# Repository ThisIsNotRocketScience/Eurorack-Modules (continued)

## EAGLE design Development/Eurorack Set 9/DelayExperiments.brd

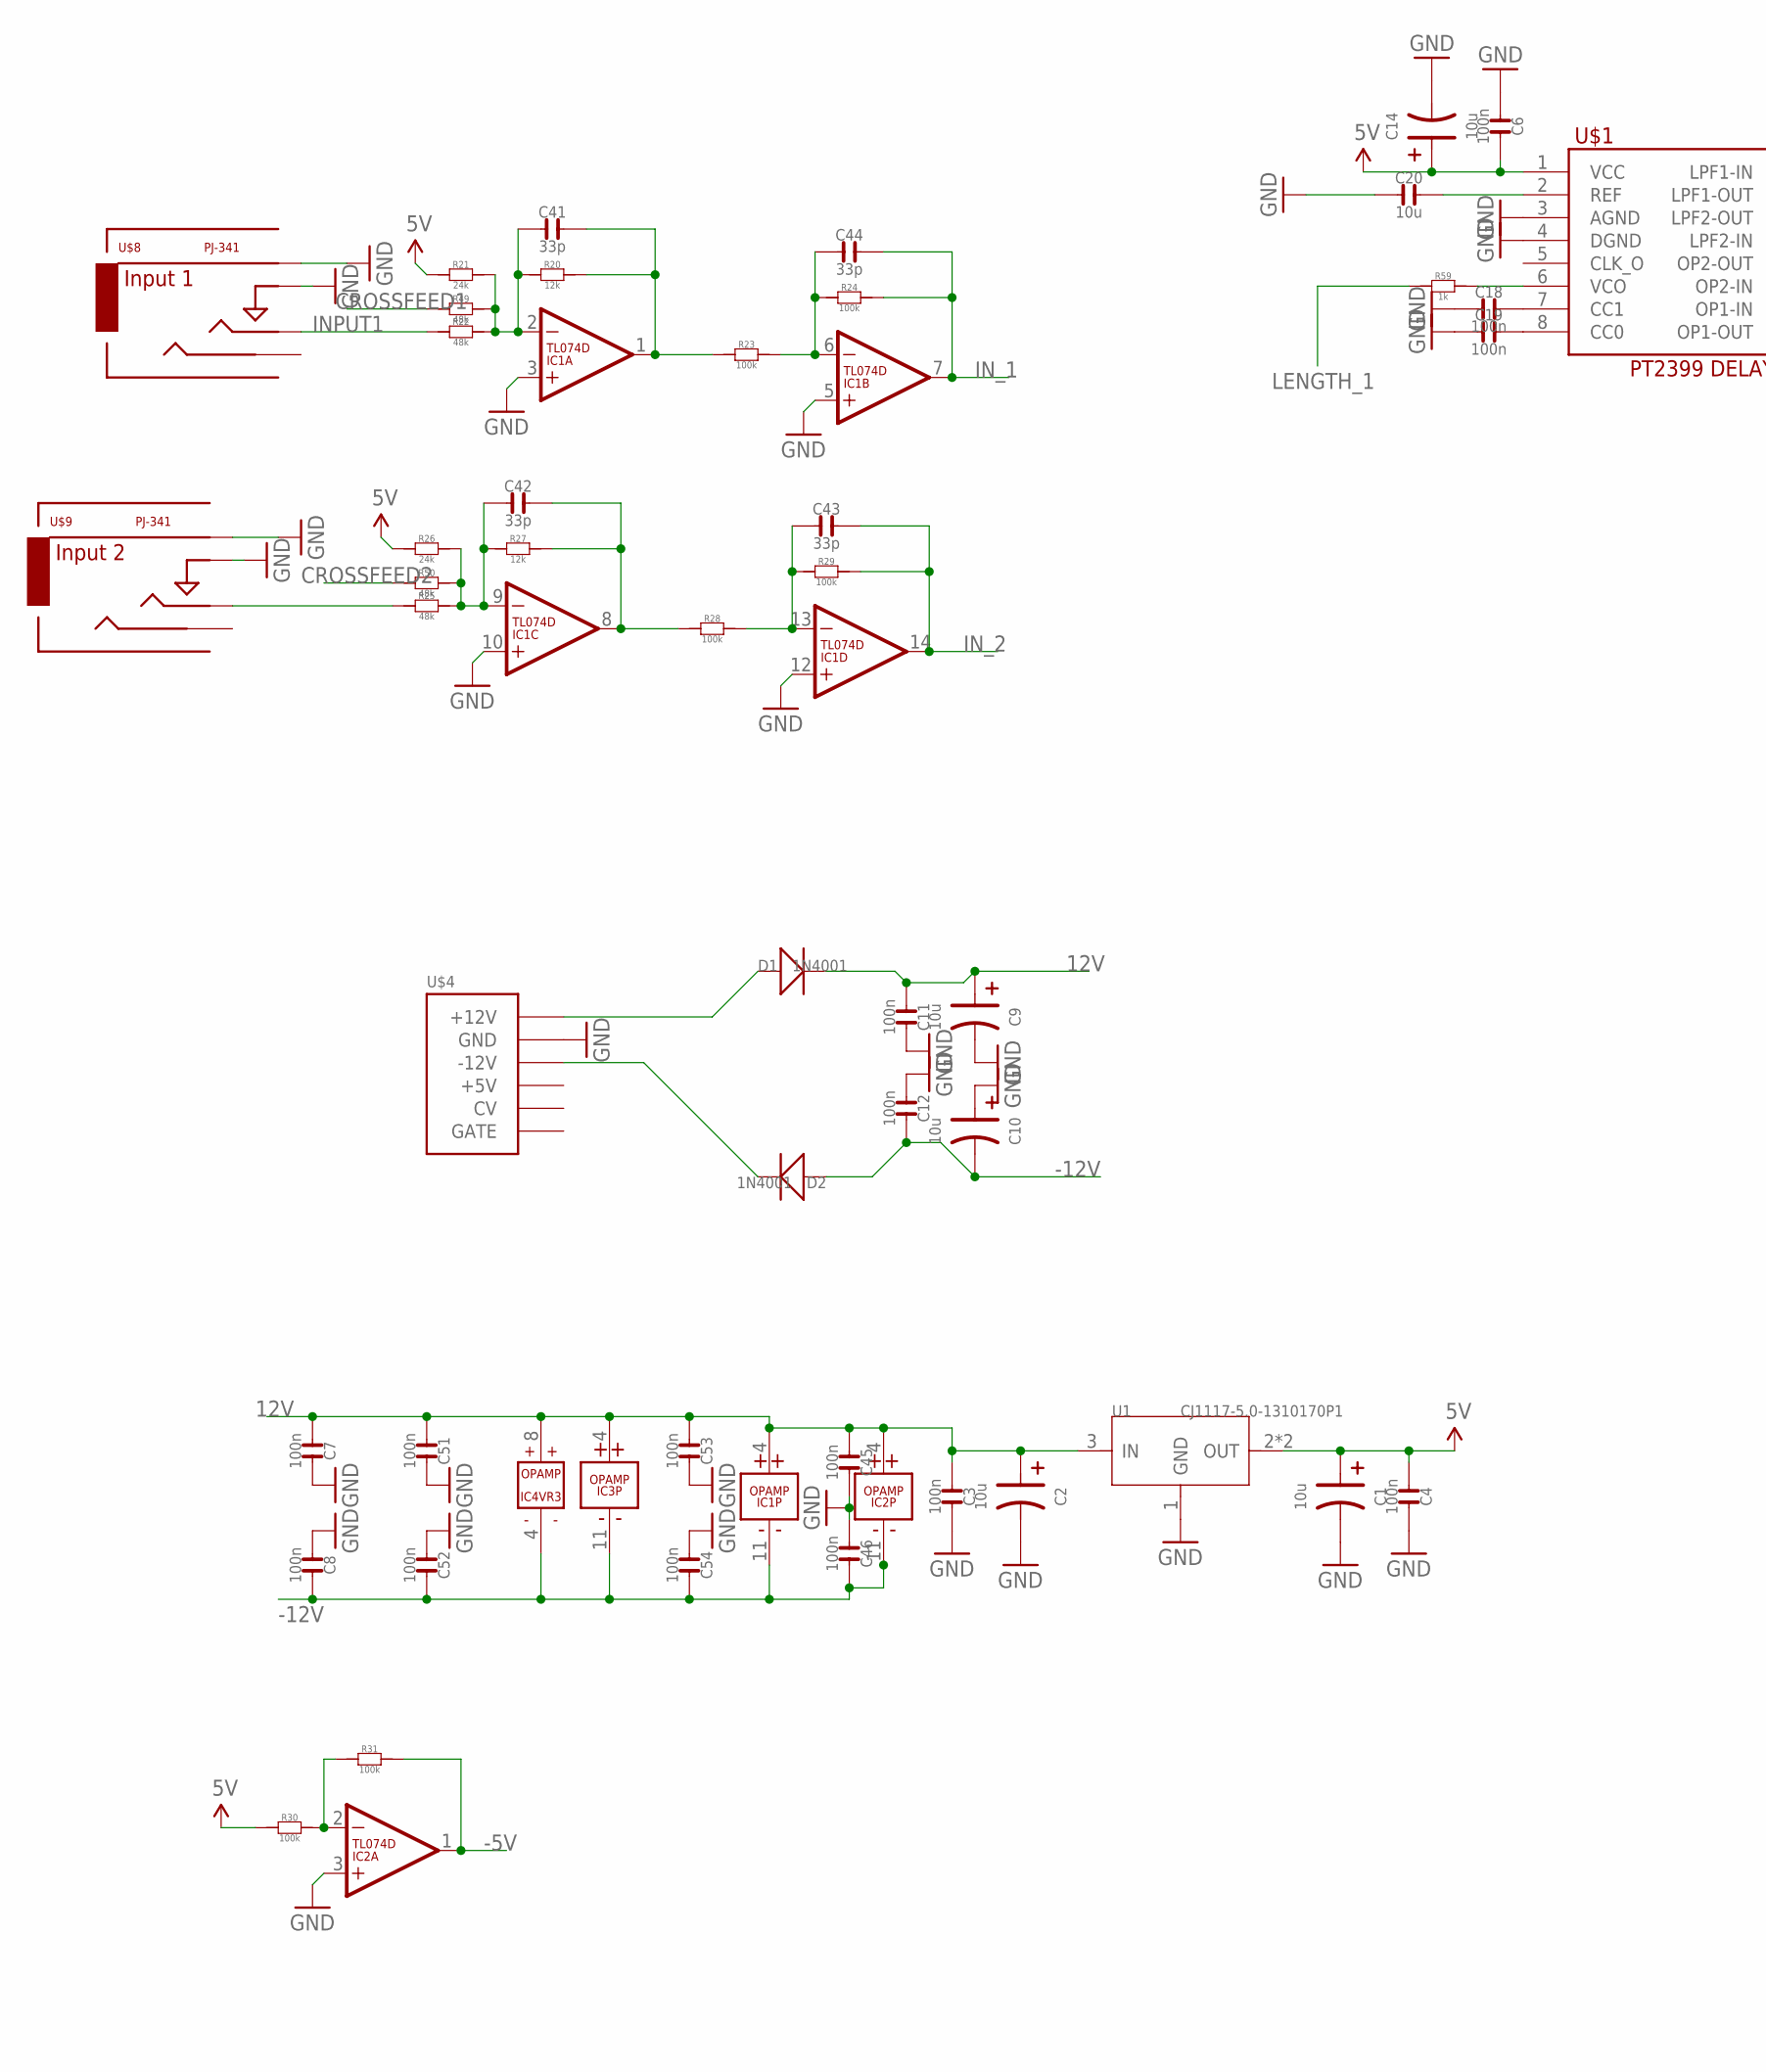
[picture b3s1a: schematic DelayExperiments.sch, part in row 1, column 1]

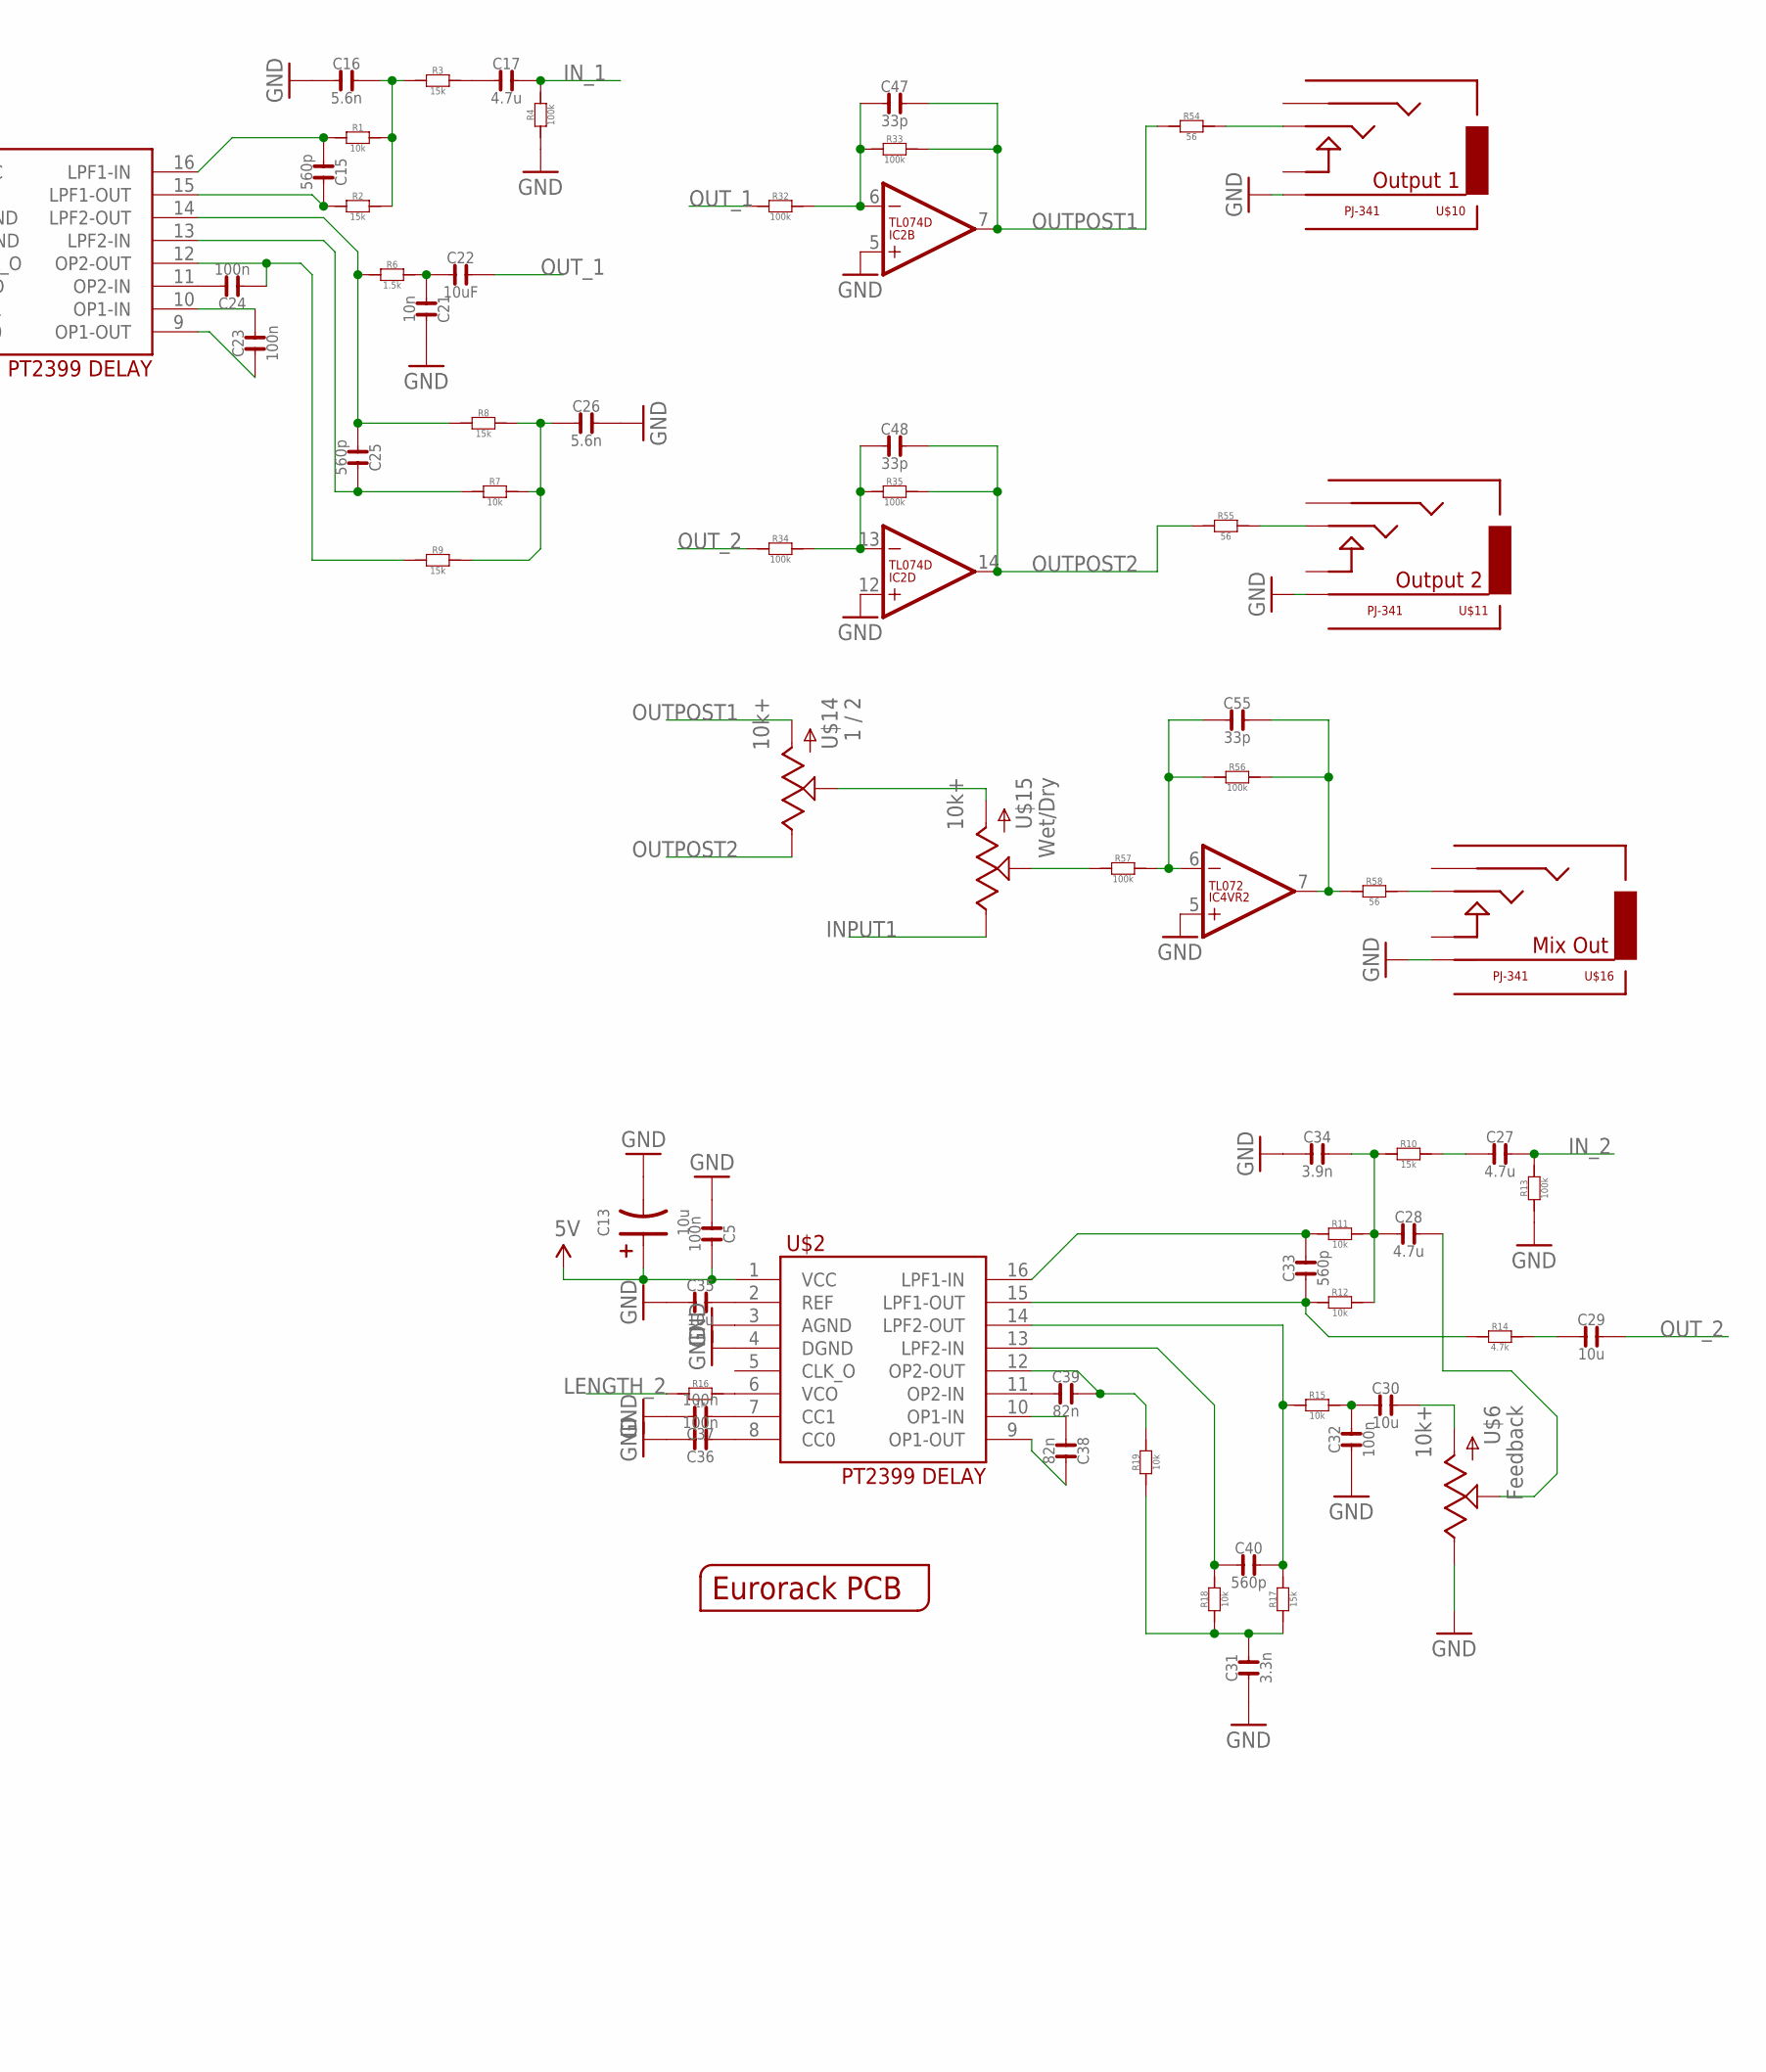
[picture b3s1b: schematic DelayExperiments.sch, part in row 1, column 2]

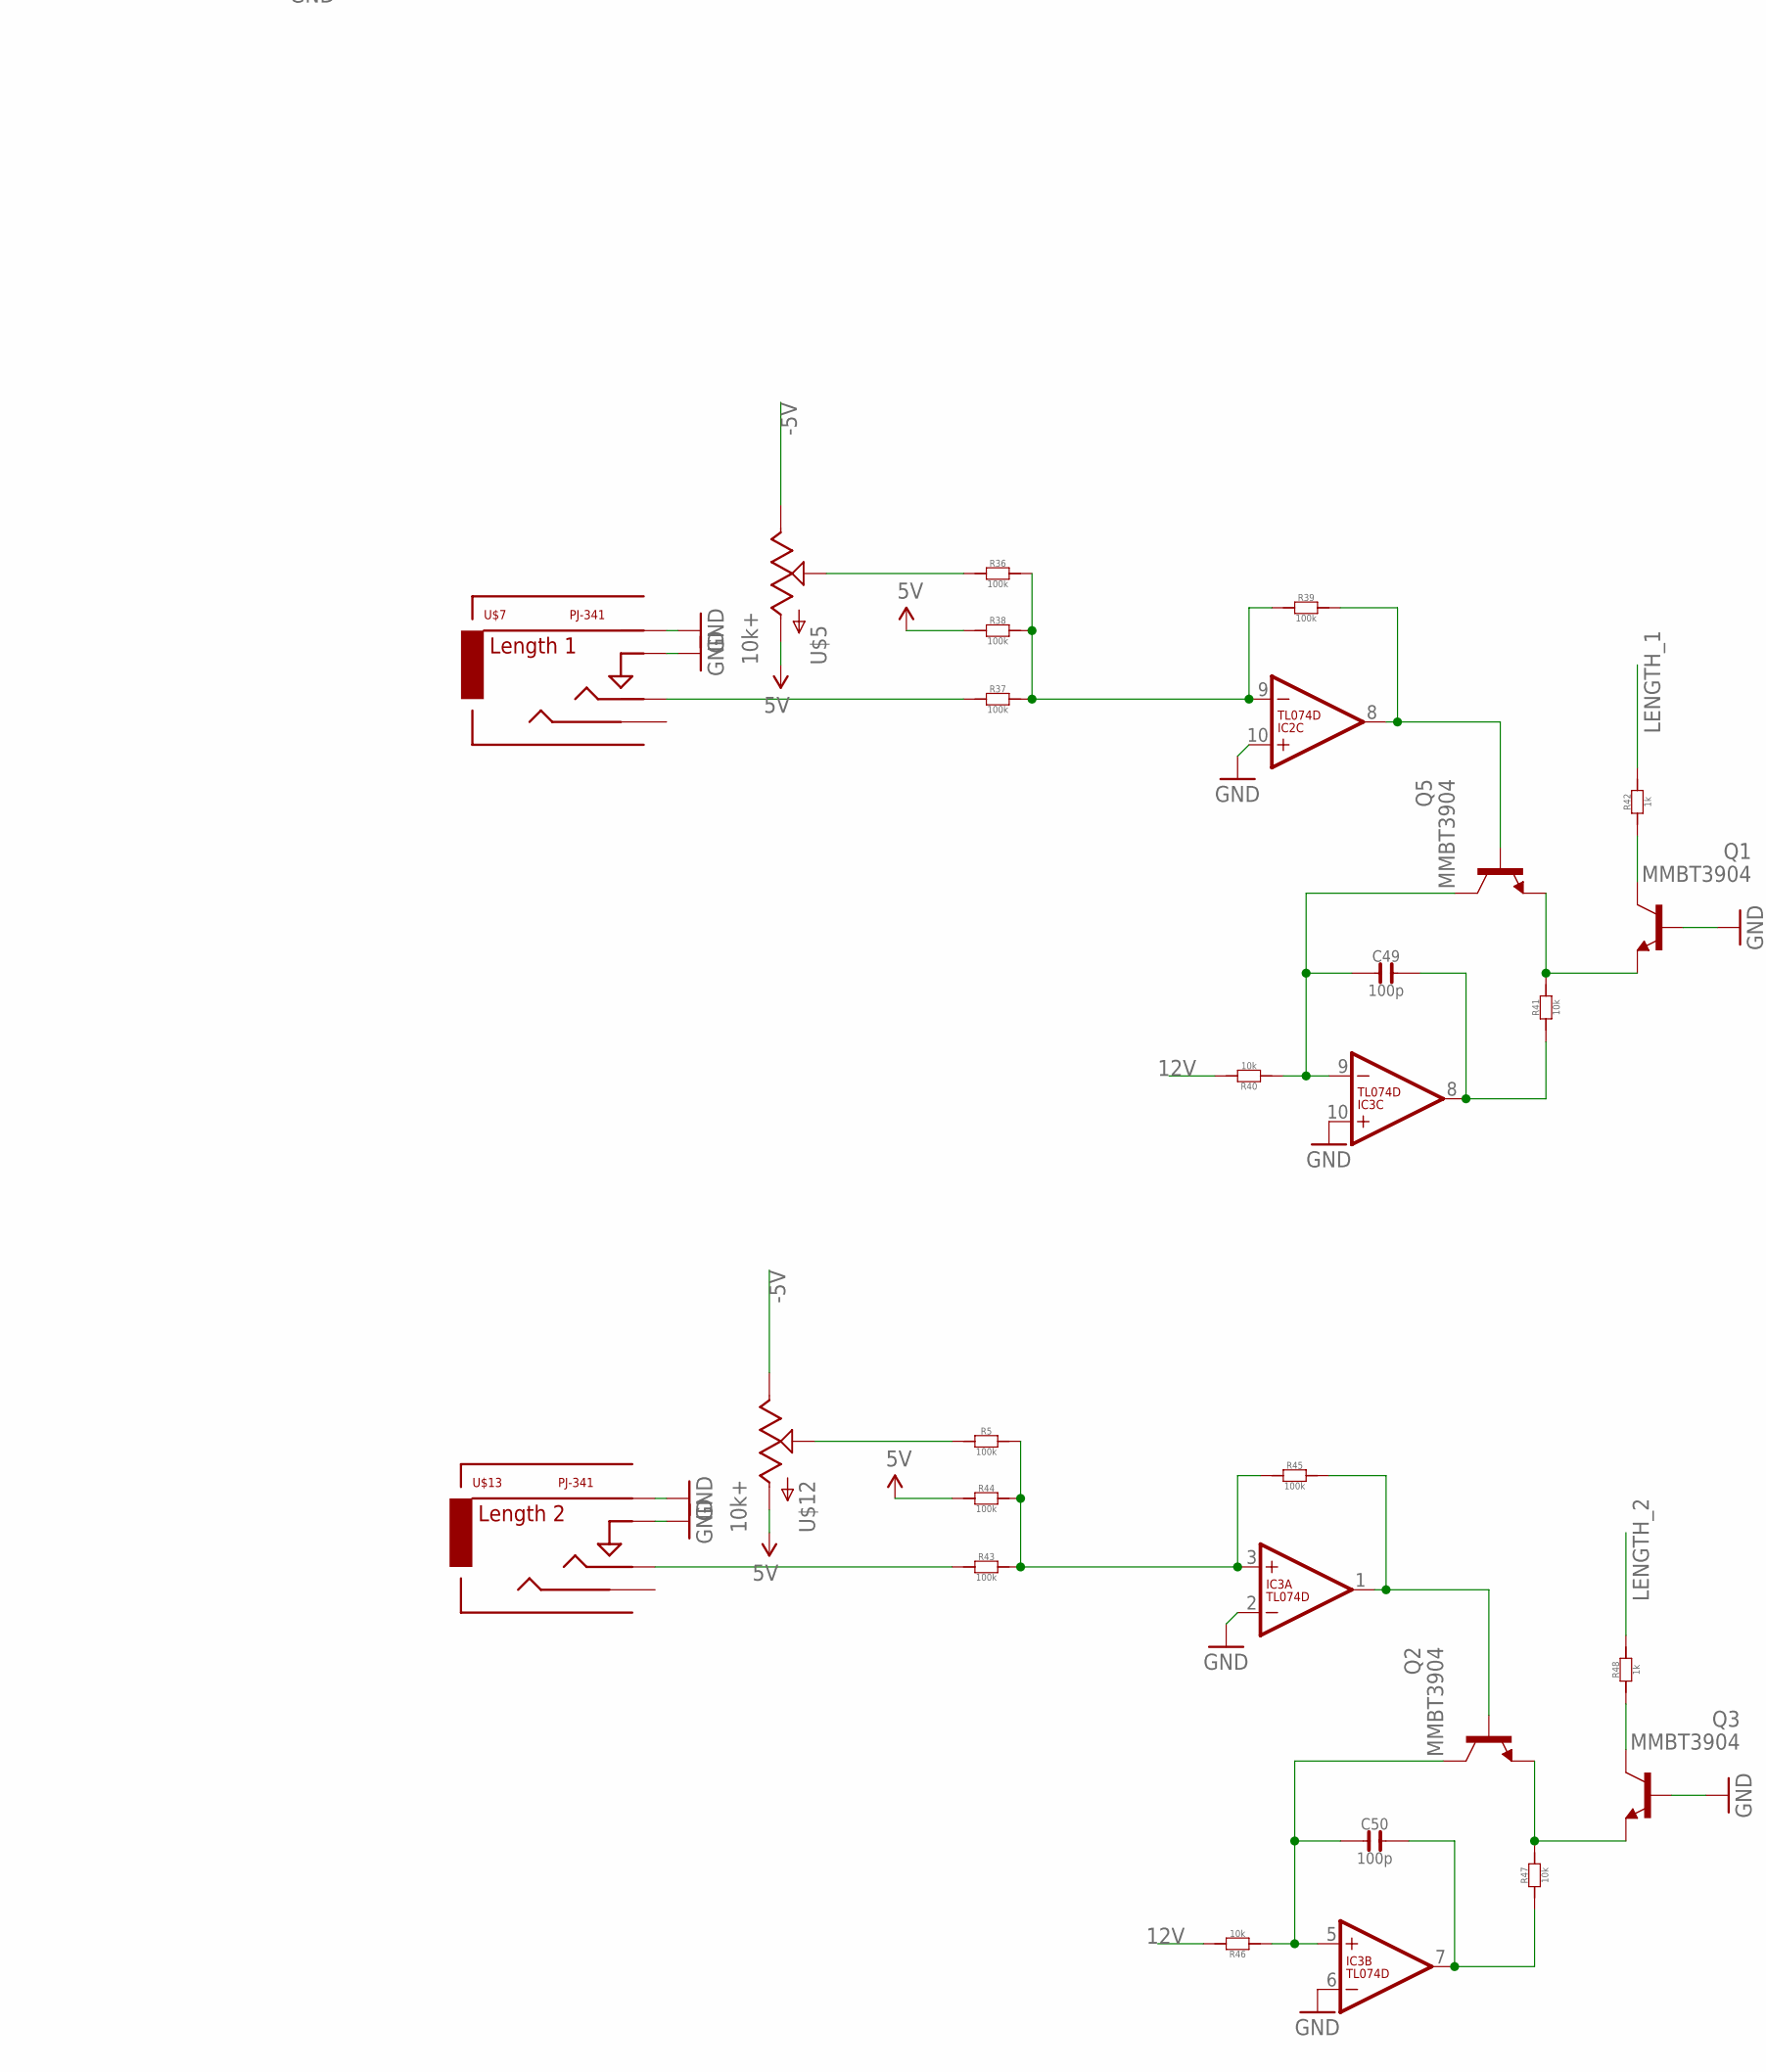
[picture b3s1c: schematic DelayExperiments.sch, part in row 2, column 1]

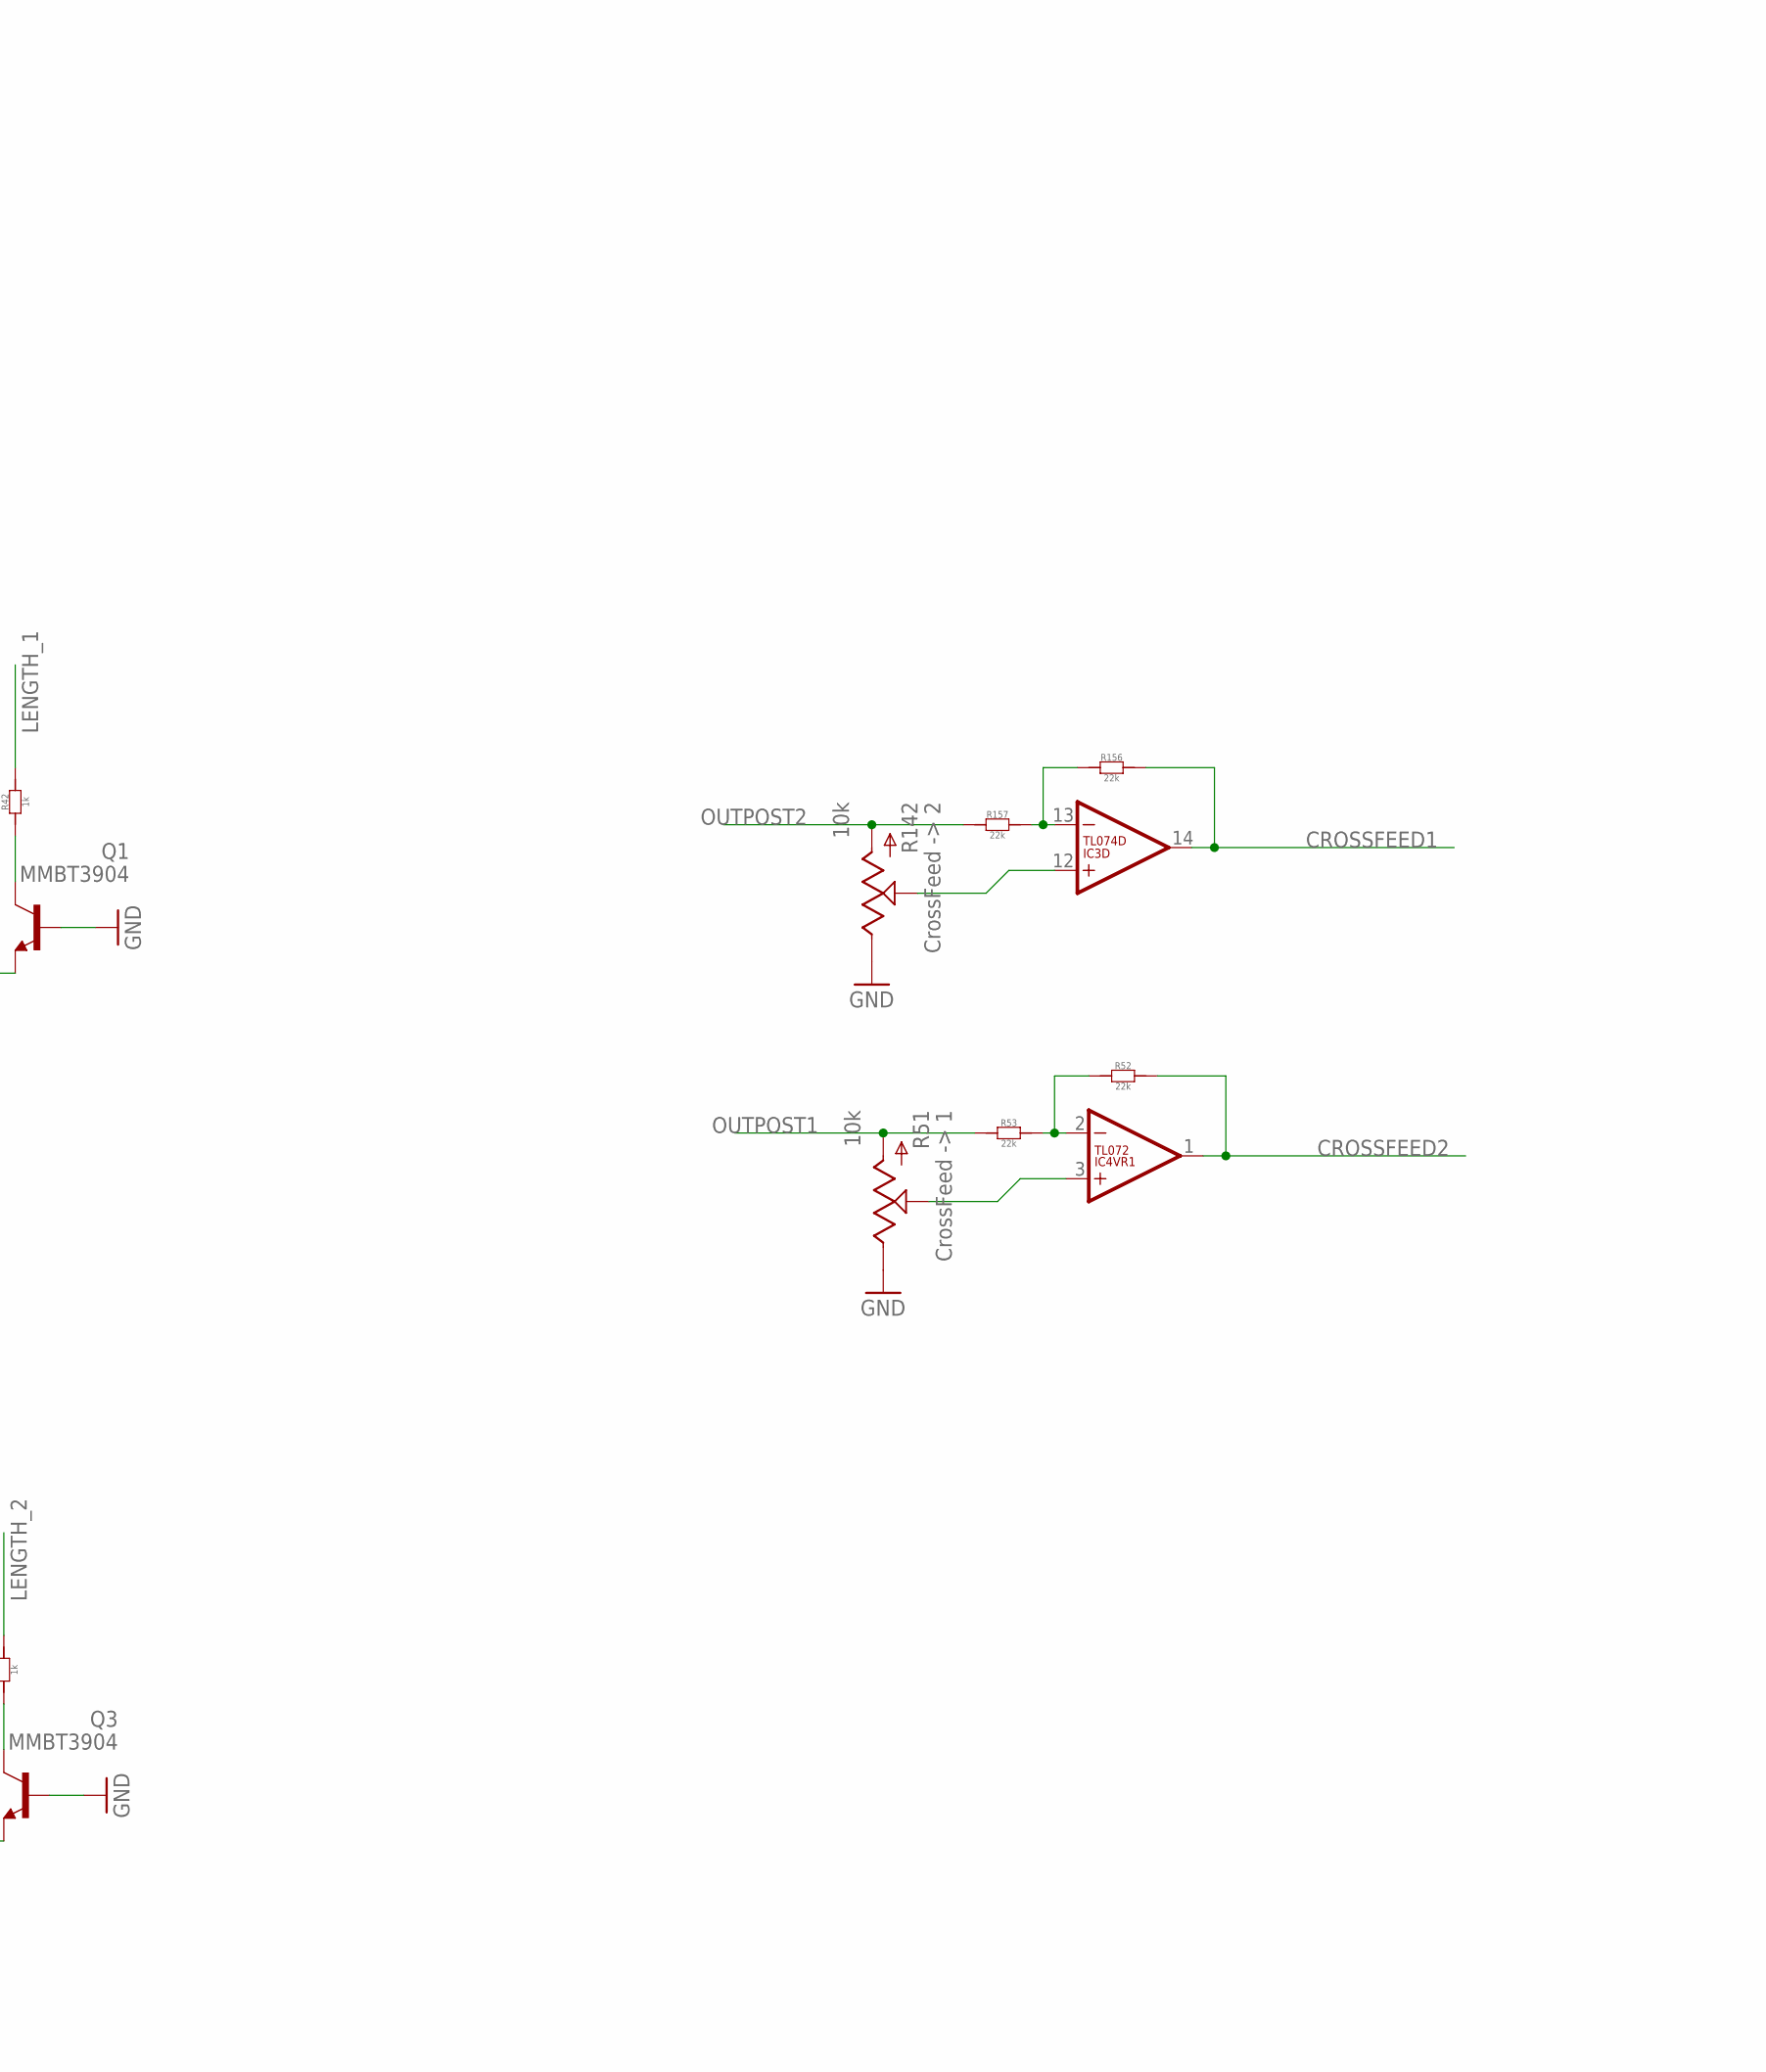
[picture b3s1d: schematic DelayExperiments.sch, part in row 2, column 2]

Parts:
C1, C2, C9, C10, C13, C14: 10u; CASE-A_3216
C3, C4, C5, C6, C7, C8, C11, C12, C18, C19, C23, C24, C32, C36, C37, C45, C46, C51, C52, C53, C54: 100n; C0603
C15, C25, C33, C40: 560p; C0603
C16, C26: 5.6n; C0603
C17, C27, C28: 4.7u; C0603
C20, C29, C30, C35: 10u; C0603
C21: 10n; C0603
C22: 10uF; C0603
C31: 3.3n; C0603
C34: 3.9n; C0603
C38, C39: 82n; C0603
C41, C42, C43, C44, C47, C48, C55: 33p; C0603
C49, C50: 100p; C0603
D1, D2: 1N4001; SOD123
IC1, IC2, IC3: TL074D; SO14
IC4: TL072; SO08
Q1, Q2, Q3, Q5: MMBT3904; SOT23-BEC; MPN PMBT3904,215
R1, R7, R11, R12, R15, R18, R19, R40, R41, R46, R47: 10k; R0603
R2, R3, R8, R9, R10, R17: 15k; R0603
R4, R5, R13, R23, R24, R28, R29, R30, R31, R32, R33, R34, R35, R36, R37, R38, R39, R43, R44, R45, R56, R57: 100k; R0603
R6: 1.5k; R0603
R14: 4.7k; R0603
R16, R42, R48, R59: 1k; R0603
R20, R27: 12k; R0603
R21, R26: 24k; R0603
R22, R25, R49, R50: 48k; R0603
R51, R142: 10k; OG-POTS_ALPS_POT_VERTICAL
R52, R53, R156, R157: 22k; R0603
R54, R55, R58: 56; R0603
U1: CJ1117-5.0-1310170P1; SOT223
U$1, U$2: PT2399; SO16
U$3: EURORACK_PCB12HP; EURORACK12HPPCB
U$4: POWERSHROUDED; POWER_16_SHROUDED
U$5, U$12: 10k+; OG-POTS_ALPS_POT_VERTICAL_WITHBIGKNOB
U$6, U$14, U$15: 10k+; OG-POTS_ALPS_POT_VERTICAL
U$7, U$8, U$9, U$13: PJ-341; 3.5MM-JACK-SWITCH-13MM-INPUT
U$10, U$11, U$16: PJ-341; 3.5MM-JACK-SWITCH-13MM-OUTPUT

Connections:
5V: C1.+ (1), C4.1, C5.2, C6.2, C13.+ (1), C14.+ (1), R21.1, R26.1, R30.1, R38.1, R44.1, U1.2 (OUT), U1.TER (OUT), U$1.1 (VCC), U$2.1 (VCC), U$5.P$3 (A), U$12.P$3 (A)
12V: C2.+ (1), C3.1, C7.1, C9.+ (1), C11.1, C45.1, C51.1, C53.1, D1.-, IC1.4 (V+), IC2.4 (V+), IC3.4 (V+), IC4.8 (V+), R40.2, R46.2, U1.3 (IN)
-5V: IC2.1 (OUT), R31.2, U$5.P$1 (E), U$12.P$1 (E)
-12V: C8.2, C10.- (2), C12.2, C46.2, C52.2, C54.2, D2.+, IC1.11 (V-), IC2.11 (V-), IC3.11 (V-), IC4.4 (V-)
CROSSFEED1: IC3.14 (OUT), R49.1, R156.2
CROSSFEED2: IC4.1 (OUT), R50.1, R52.2
GND: C1.- (2), C2.- (2), C3.2, C4.2, C5.1, C6.1, C7.2, C8.1, C9.- (2), C10.+ (1), C11.2, C12.1, C13.- (2), C14.- (2), C16.1, C18.1, C19.1, C20.1, C21.2, C26.2, C31.1, C32.1, C34.1, C35.1, C36.2, C37.2, C45.2, C46.1, C51.2, C52.1, C53.2, C54.1, IC1.3 (+IN), IC1.5 (+IN), IC1.10 (+IN), IC1.12 (+IN), IC2.3 (+IN), IC2.5 (+IN), IC2.10 (+IN), IC2.12 (+IN), IC3.2 (-IN), IC3.6 (-IN), IC3.10 (+IN), IC4.5 (+IN), Q1.B, Q3.B, R4.1, R13.1, R51.P$1 (E), R142.P$1 (E), U1.1 (GND), U$1.3 (AGND), U$1.4 (DGND), U$2.3 (AGND), U$2.4 (DGND), U$4.3 (GND), U$4.4 (GND), U$4.5 (GND), U$4.6 (GND), U$4.7 (GND), U$4.8 (GND), U$6.P$1 (E), U$7.RING@3 (RING), U$7.SWITCH@3 (SWITCH), U$8.RING@3 (RING), U$8.SWITCH@3 (SWITCH), U$9.RING@3 (RING), U$9.SWITCH@3 (SWITCH), U$10.RING@3 (RING), U$11.RING@3 (RING), U$13.RING@3 (RING), U$13.SWITCH@3 (SWITCH), U$16.RING@3 (RING)
INPUT1: R22.1, U$8.TIP@3 (TIP), U$15.P$1 (E)
IN_1: C17.2, C44.2, IC1.7 (OUT), R4.2, R24.2
IN_2: C27.2, C43.2, IC1.14 (OUT), R13.2, R29.2
LENGTH_1: R42.2, R59.1
LENGTH_2: R16.1, R48.2
unnamed: D1.+, U$4.9 (+12V), U$4.10 (+12V)
unnamed: C15.1, R1.1, U$1.16 (LPF1-IN)
unnamed: C15.2, R2.1, U$1.15 (LPF1-OUT)
unnamed: C17.1, R3.2
unnamed: D2.-, U$4.1 (-12V), U$4.2 (-12V)
unnamed: C18.2, U$1.7 (CC1)
unnamed: C16.2, R1.2, R2.2, R3.1
unnamed: C19.2, U$1.8 (CC0)
unnamed: C20.2, U$1.2 (REF)
unnamed: C21.1, C22.1, R6.2
unnamed: R36.1, U$5.P$2 (S)
unnamed: R5.1, U$12.P$2 (S)
unnamed: C25.1, R6.1, R8.1, U$1.14 (LPF2-OUT)
unnamed: C24.2, U$1.11 (OP2-IN)
unnamed: C23.2, U$1.10 (OP1-IN)
unnamed: C23.1, U$1.9 (OP1-OUT)
unnamed: C25.2, R7.1, U$1.13 (LPF2-IN)
unnamed: C26.1, R7.2, R8.2, R9.2
unnamed: C24.1, R9.1, U$1.12 (OP2-OUT)
unnamed: C28.2, U$6.P$2 (S)
unnamed: C27.1, R10.2
unnamed: C33.1, R12.1, R14.1, U$2.15 (LPF1-OUT)
unnamed: C33.2, R11.1, U$2.16 (LPF1-IN)
unnamed: C28.1, C34.2, R10.1, R11.2, R12.2
unnamed: C30.2, U$6.P$3 (A)
unnamed: C29.1, R14.2
unnamed: C30.1, C32.2, R15.2
unnamed: C40.2, R15.1, R17.2, U$2.14 (LPF2-OUT)
unnamed: C35.2, U$2.2 (REF)
unnamed: C36.1, U$2.8 (CC0)
unnamed: C37.1, U$2.7 (CC1)
unnamed: R16.2, U$2.6 (VCO)
unnamed: R37.1, U$7.TIP@3 (TIP)
unnamed: C38.1, U$2.10 (OP1-IN)
unnamed: C38.2, U$2.9 (OP1-OUT)
unnamed: C39.1, U$2.11 (OP2-IN)
unnamed: C39.2, R19.2, U$2.12 (OP2-OUT)
unnamed: C40.1, R18.2, U$2.13 (LPF2-IN)
unnamed: C31.2, R17.1, R18.1, R19.1
unnamed: C43.1, IC1.13 (-IN), R28.2, R29.1
unnamed: C44.1, IC1.6 (-IN), R23.2, R24.1
unnamed: C41.1, IC1.2 (-IN), R20.1, R21.2, R22.2, R49.2
unnamed: C41.2, IC1.1 (OUT), R20.2, R23.1
unnamed: IC2.2 (-IN), R30.2, R31.1
unnamed: IC4.2 (-IN), R52.1, R53.2
unnamed: C42.2, IC1.8 (OUT), R27.2, R28.1
unnamed: C42.1, IC1.9 (-IN), R25.2, R26.2, R27.1, R50.2
unnamed: R59.2, U$1.6 (VCO)
unnamed: R25.1, U$9.TIP@3 (TIP)
unnamed: C47.1, IC2.6 (-IN), R32.2, R33.1
unnamed: C48.1, IC2.13 (-IN), R34.2, R35.1
unnamed: IC2.9 (-IN), R36.2, R37.2, R38.2, R39.1
unnamed: IC2.8 (OUT), Q5.B, R39.2
unnamed: C49.1, IC3.9 (-IN), Q5.C, R40.1
unnamed: IC4.3 (+IN), R51.P$2 (S)
unnamed: U$14.P$2 (S), U$15.P$3 (A)
unnamed: Q1.C, R42.1
unnamed: C49.2, IC3.8 (OUT), R41.1
unnamed: Q1.E, Q5.E, R41.2
unnamed: R43.1, U$13.TIP@3 (TIP)
unnamed: IC3.3 (+IN), R5.2, R43.2, R44.2, R45.1
unnamed: IC3.1 (OUT), Q2.B, R45.2
unnamed: C50.1, IC3.5 (+IN), Q2.C, R46.1
unnamed: Q3.C, R48.1
unnamed: C50.2, IC3.7 (OUT), R47.1
unnamed: Q2.E, Q3.E, R47.2
unnamed: R55.2, U$11.TIP@3 (TIP)
unnamed: R54.2, U$10.TIP@3 (TIP)
unnamed: C55.2, IC4.7 (OUT), R56.2, R58.1
unnamed: R58.2, U$16.TIP@3 (TIP)
unnamed: R57.1, U$15.P$2 (S)
unnamed: IC3.13 (-IN), R156.1, R157.2
unnamed: C55.1, IC4.6 (-IN), R56.1, R57.2
unnamed: IC3.12 (+IN), R142.P$2 (S)
OUTPOST1: C47.2, IC2.7 (OUT), R33.2, R51.P$3 (A), R53.1, R54.1, U$14.P$3 (A)
OUTPOST2: C48.2, IC2.14 (OUT), R35.2, R55.1, R142.P$3 (A), R157.1, U$14.P$1 (E)
OUT_1: C22.2, R32.1
OUT_2: C29.2, R34.1

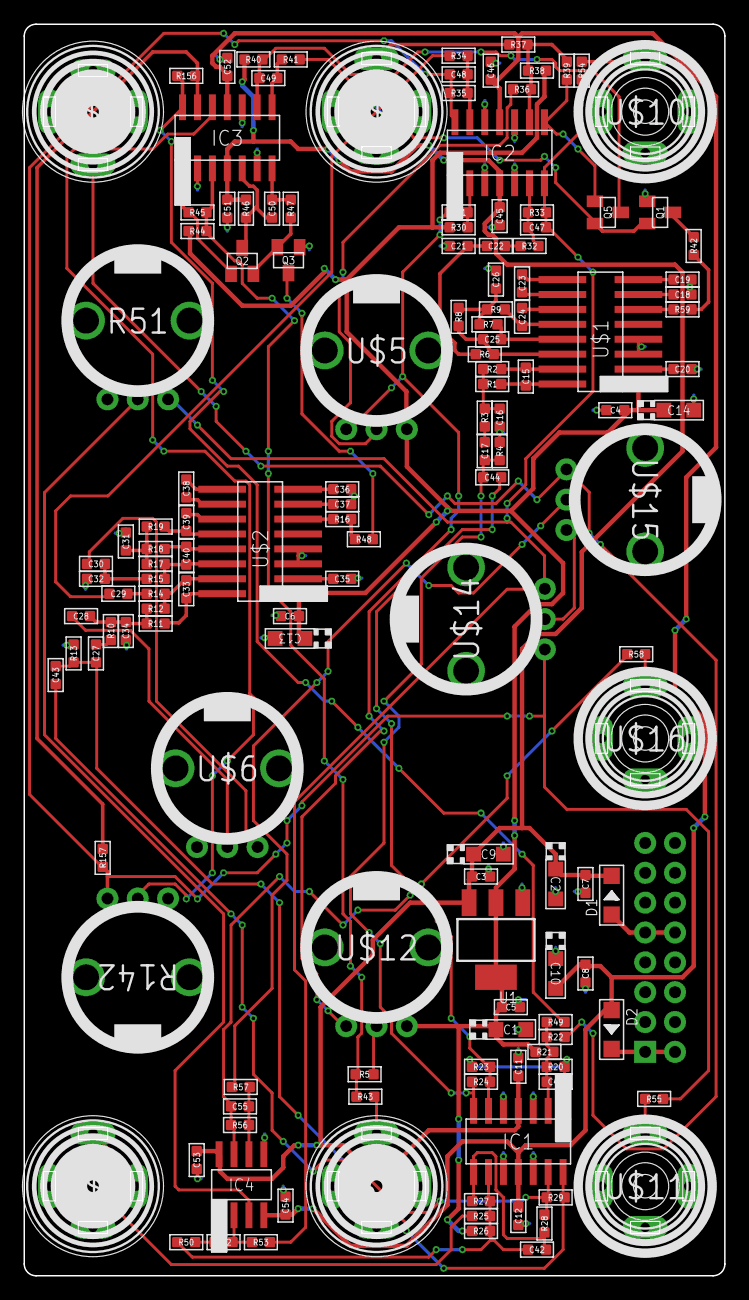
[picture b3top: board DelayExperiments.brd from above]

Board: 2 copper layers, 59.6 x 106.5 mm, 144 parts (1 on the bottom side), 90 nets.

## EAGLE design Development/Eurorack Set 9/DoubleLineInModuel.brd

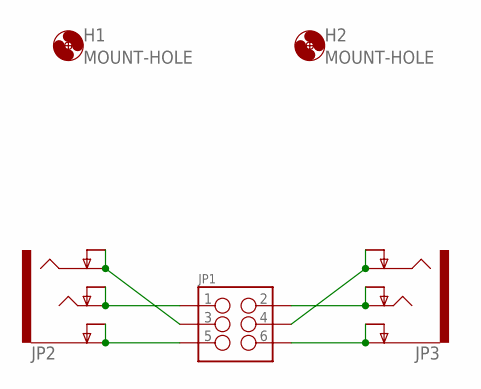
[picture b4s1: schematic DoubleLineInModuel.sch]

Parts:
H1, H2: MOUNT-HOLE; 3.2-NOMARKINGS-SMALLSAFEZONE
JP1: M03X2; 2X3-SHROUDED
JP2, JP3: AUDIO-JACK4-.25-HORIZ-TRS; AUDIO-JACK-.25-INCH-HORIZ-PTH

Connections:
unnamed: JP1.1, JP2.P$6 (TIP), JP2.P$7 (TIP-NORM)
unnamed: JP1.3, JP2.P$4 (RING), JP2.P$5 (RING-NORM)
unnamed: JP1.5, JP2.P$2 (EARTH), JP2.P$3 (EARTH-NORM)
unnamed: JP1.6, JP3.P$2 (EARTH), JP3.P$3 (EARTH-NORM)
unnamed: JP1.2, JP3.P$6 (TIP), JP3.P$7 (TIP-NORM)
unnamed: JP1.4, JP3.P$4 (RING), JP3.P$5 (RING-NORM)

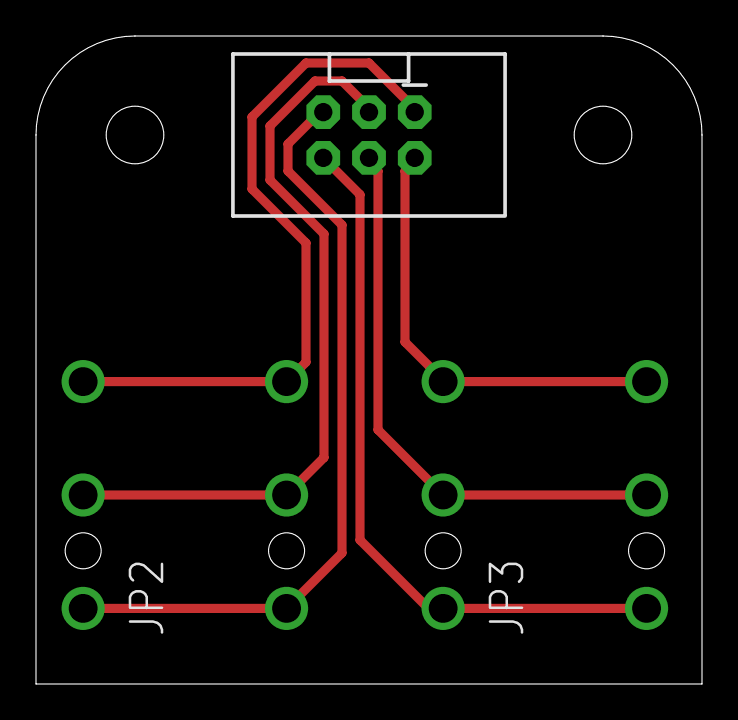
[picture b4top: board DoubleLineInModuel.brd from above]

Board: 2 copper layers, 37.0 x 36.0 mm, 5 parts (0 on the bottom side), 6 nets.

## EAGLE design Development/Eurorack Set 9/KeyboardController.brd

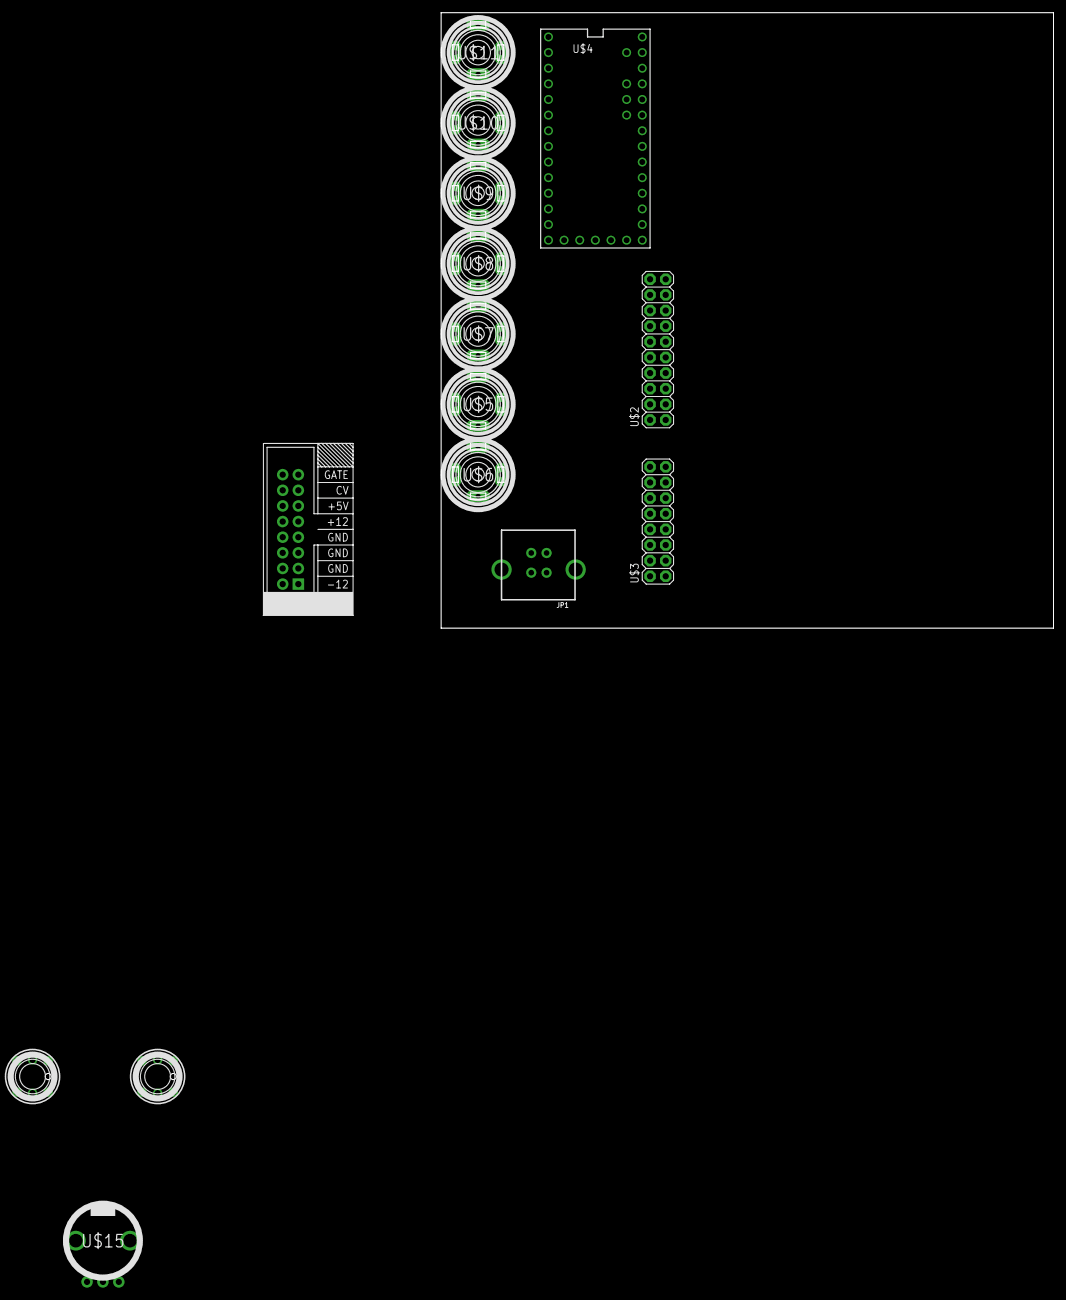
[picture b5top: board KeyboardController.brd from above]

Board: 2 copper layers, 99.5 x 100.0 mm, 16 parts (0 on the bottom side), 2 nets, no tracks yet.

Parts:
JP1: USBPTH-VERTICAL; USB-B-PTH-VERTICAL
U$1: EURORACK_PCB20HP_10X10CM; EURORACK20HP_10X10CM
U$2: M10X2; 2X10
U$3: M08X2; 2X8
U$4: TEENSY_3.1-3.2_ALL_PINS; TEENSY_3.0-3.2&LC_ALL_PINS
U$5, U$6, U$7, U$8, U$9, U$10, U$11: PJ-341; 3.5MM-JACK-SWITCH-13MM-OUTPUT
U$12: POWERSHROUDED; POWER_16_SHROUDED
U$13, U$14: SWITCH_W_LED_PB6149L-X-102YELLOW; PB6149L
U$15: OG-POTS_ALPS_POT_VERTICAL

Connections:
3.3V: U$3.5, U$4.3.3V, U$4.3.3V1
GND: U$3.6, U$3.11, U$4.GND, U$4.GND1, U$12.3, U$12.4, U$12.5, U$12.6, U$12.7, U$12.8
